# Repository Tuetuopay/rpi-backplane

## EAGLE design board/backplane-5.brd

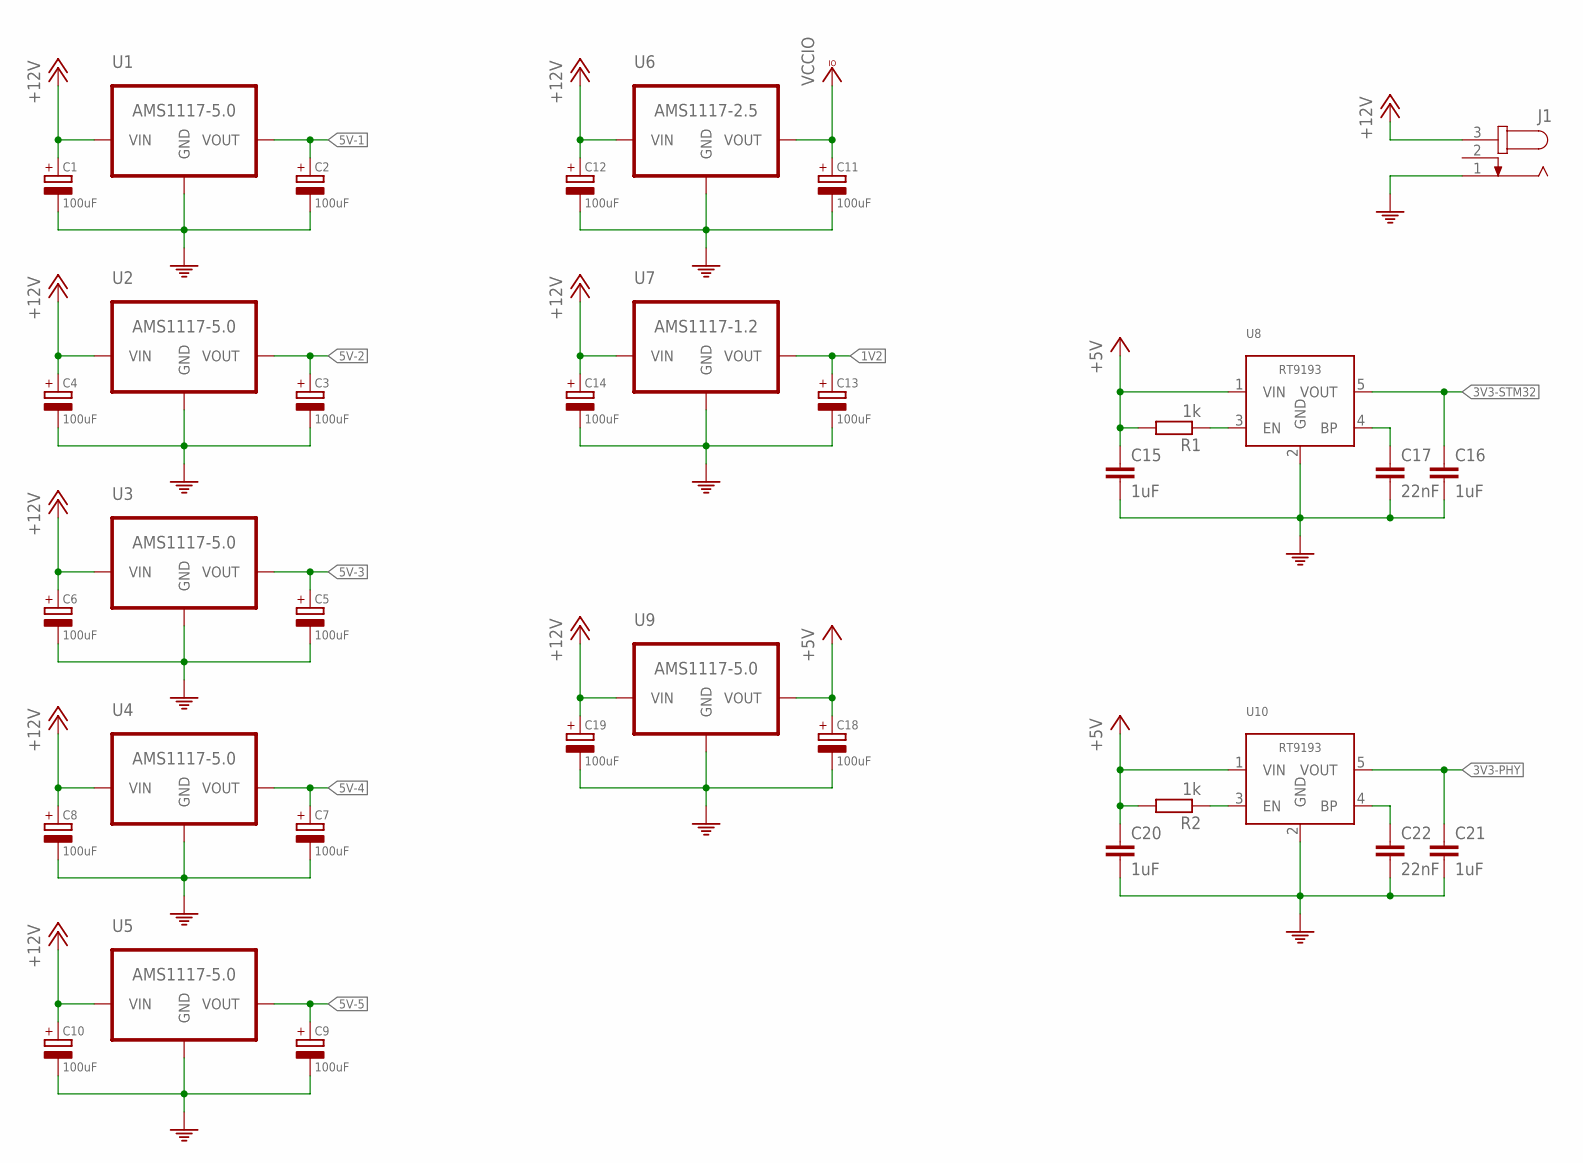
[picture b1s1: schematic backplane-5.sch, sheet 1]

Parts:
C1, C2, C3, C4, C5, C6, C7, C8, C9, C10, C11, C12, C13, C14, C18, C19: 100uF; CAP-D6.3
C15, C16, C20, C21: 1uF; C0603
C17, C22: 22nF; C0603
J1: JACK-PLUG0; SPC4077
R1, R2: 1k; R0603
U1, U2, U3, U4, U5, U9: AMS1117-5.0; SOT223
U6: AMS1117-2.5; SOT223
U7: AMS1117-1.2; SOT223
U8, U10: RT9193; SOT23-5

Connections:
1V2: C13.P (POS), U7.2 (VOUT); also elsewhere on the board
3V3-PHY: C21.1, U10.5 (VOUT); also elsewhere on the board
3V3-STM32: C16.1, U8.5 (VOUT)
5V-1: C2.P (POS), U1.2 (VOUT); also elsewhere on the board
5V-2: C3.P (POS), U2.2 (VOUT); also elsewhere on the board
5V-3: C5.P (POS), U3.2 (VOUT); also elsewhere on the board
5V-4: C7.P (POS), U4.2 (VOUT); also elsewhere on the board
5V-5: C9.P (POS), U5.2 (VOUT); also elsewhere on the board
+5V: C15.1, C18.P (POS), C20.1, R1.2, R2.2, U8.1 (VIN), U9.2 (VOUT), U10.1 (VIN)
+12V: C1.P (POS), C4.P (POS), C6.P (POS), C8.P (POS), C10.P (POS), C12.P (POS), C14.P (POS), C19.P (POS), J1.3, U1.3 (VIN), U2.3 (VIN), U3.3 (VIN), U4.3 (VIN), U5.3 (VIN), U6.3 (VIN), U7.3 (VIN), U9.3 (VIN)
GND: C1.N (NEG), C2.N (NEG), C3.N (NEG), C4.N (NEG), C5.N (NEG), C6.N (NEG), C7.N (NEG), C8.N (NEG), C9.N (NEG), C10.N (NEG), C11.N (NEG), C12.N (NEG), C13.N (NEG), C14.N (NEG), C15.2, C16.2, C17.2, C18.N (NEG), C19.N (NEG), C20.2, C21.2, C22.2, J1.1, U1.1 (GND), U2.1 (GND), U3.1 (GND), U4.1 (GND), U5.1 (GND), U6.1 (GND), U7.1 (GND), U8.2 (GND), U9.1 (GND), U10.2 (GND); also elsewhere on the board
unnamed: C17.1, U8.4 (BP)
unnamed: R1.1, U8.3 (EN)
unnamed: C22.1, U10.4 (BP)
unnamed: R2.1, U10.3 (EN)
VCCIO: C11.P (POS), U6.2 (VOUT); also elsewhere on the board

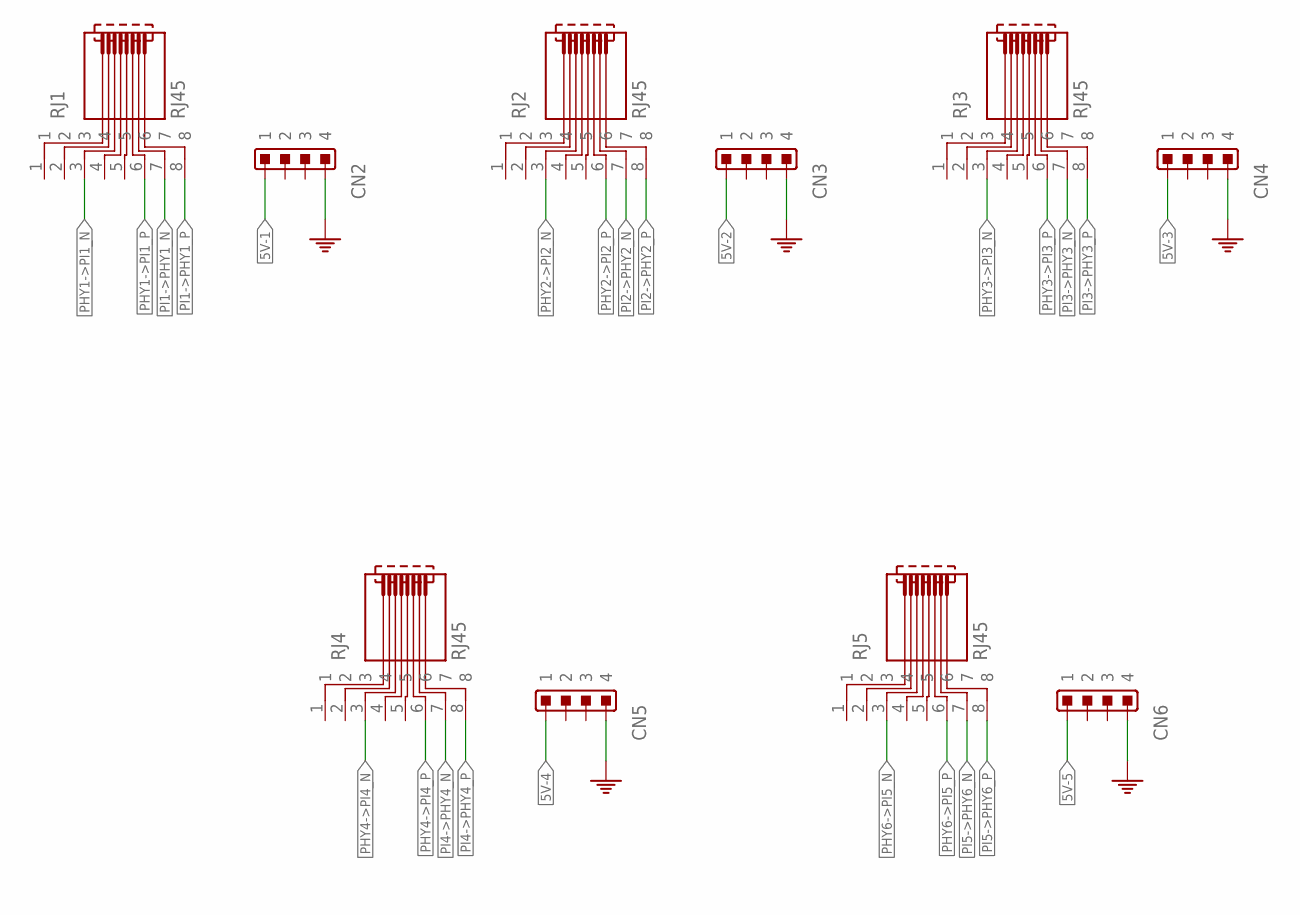
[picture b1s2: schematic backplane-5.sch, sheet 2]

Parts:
CN2, CN3, CN4, CN5, CN6: 4PINCONNFEMALE-1.6; 4PINCONN-FEMALE-1.6
RJ1, RJ2, RJ3, RJ4, RJ5: RJ45PLUG; RJ45MALE

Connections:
5V-1: CN2.1@1 (1), CN2.1@2 (1); also elsewhere on the board
5V-2: CN3.1@1 (1), CN3.1@2 (1); also elsewhere on the board
5V-3: CN4.1@1 (1), CN4.1@2 (1); also elsewhere on the board
5V-4: CN5.1@1 (1), CN5.1@2 (1); also elsewhere on the board
5V-5: CN6.1@1 (1), CN6.1@2 (1); also elsewhere on the board
GND: CN2.4@1 (4), CN2.4@2 (4), CN3.4@1 (4), CN3.4@2 (4), CN4.4@1 (4), CN4.4@2 (4), CN5.4@1 (4), CN5.4@2 (4), CN6.4@1 (4), CN6.4@2 (4); also elsewhere on the board
PHY1->PI1_N: RJ1.3; also elsewhere on the board
PHY1->PI1_P: RJ1.6; also elsewhere on the board
PHY2->PI2_N: RJ2.3; also elsewhere on the board
PHY2->PI2_P: RJ2.6; also elsewhere on the board
PHY3->PI3_N: RJ3.3; also elsewhere on the board
PHY3->PI3_P: RJ3.6; also elsewhere on the board
PHY4->PI4_N: RJ4.3; also elsewhere on the board
PHY4->PI4_P: RJ4.6; also elsewhere on the board
PHY6->PI5_N: RJ5.3; also elsewhere on the board
PHY6->PI5_P: RJ5.6; also elsewhere on the board
PI1->PHY1_N: RJ1.7; also elsewhere on the board
PI1->PHY1_P: RJ1.8; also elsewhere on the board
PI2->PHY2_N: RJ2.7; also elsewhere on the board
PI2->PHY2_P: RJ2.8; also elsewhere on the board
PI3->PHY3_N: RJ3.7; also elsewhere on the board
PI3->PHY3_P: RJ3.8; also elsewhere on the board
PI4->PHY4_N: RJ4.7; also elsewhere on the board
PI4->PHY4_P: RJ4.8; also elsewhere on the board
PI5->PHY6_N: RJ5.7; also elsewhere on the board
PI5->PHY6_P: RJ5.8; also elsewhere on the board

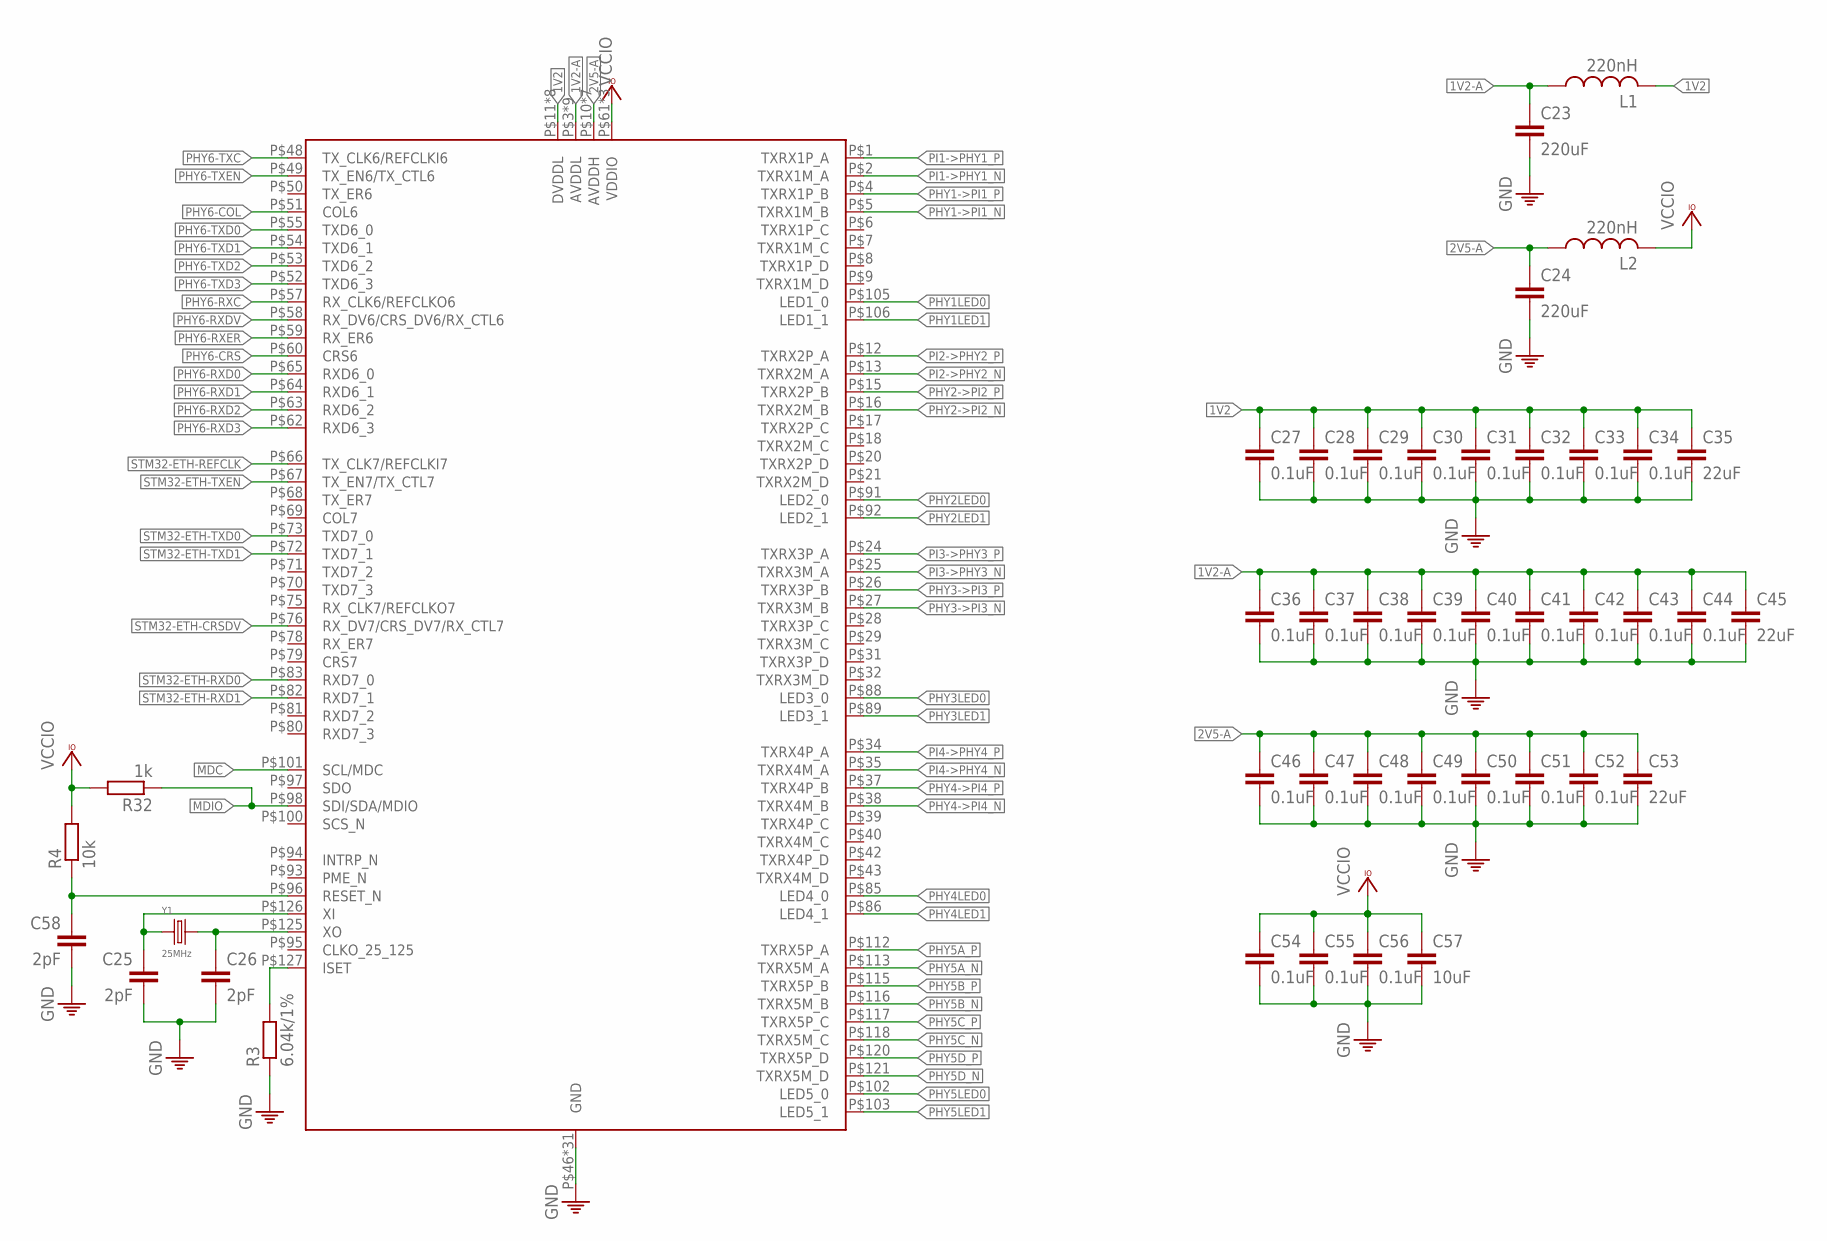
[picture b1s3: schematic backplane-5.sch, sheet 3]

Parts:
C23, C24: 220uF; 0603
C25, C26, C58: 2pF; 0603
C27, C28, C29, C30, C31, C32, C33, C34, C36, C37, C38, C39, C40, C41, C42, C43, C44, C46, C47, C48, C49, C50, C51, C52, C54, C55, C56: 0.1uF; 0603
C35, C45, C53: 22uF; 0603
C57: 10uF; 0603
L1, L2: 220nH; 1210
R3: 6.04k/1%; R0603
R4: 10k; R0603
R32: 1k; R0603
U11: KSZ9897; TQFP-128
Y1: 25MHz; XTAL-2-SMD

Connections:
1V2: C27.1, C28.1, C29.1, C30.1, C31.1, C32.1, C33.1, C34.1, C35.1, L1.2, U11.P$11 (DVDDL), U11.P$23 (DVDDL), U11.P$45 (DVDDL), U11.P$56 (DVDDL), U11.P$74 (DVDDL), U11.P$87 (DVDDL), U11.P$104 (DVDDL), U11.P$110 (DVDDL); also elsewhere on the board
1V2-A: C23.1, C36.1, C37.1, C38.1, C39.1, C40.1, C41.1, C42.1, C43.1, C44.1, C45.1, L1.1, U11.P$3 (AVDDL), U11.P$14 (AVDDL), U11.P$19 (AVDDL), U11.P$30 (AVDDL), U11.P$36 (AVDDL), U11.P$41 (AVDDL), U11.P$114 (AVDDL), U11.P$119 (AVDDL), U11.P$124 (AVDDL)
2V5-A: C24.1, C46.1, C47.1, C48.1, C49.1, C50.1, C51.1, C52.1, C53.1, L2.1, U11.P$10 (AVDDH), U11.P$22 (AVDDH), U11.P$33 (AVDDH), U11.P$44 (AVDDH), U11.P$111 (AVDDH), U11.P$122 (AVDDH), U11.P$128 (AVDDH)
GND: C23.2, C24.2, C25.2, C26.2, C27.2, C28.2, C29.2, C30.2, C31.2, C32.2, C33.2, C34.2, C35.2, C36.2, C37.2, C38.2, C39.2, C40.2, C41.2, C42.2, C43.2, C44.2, C45.2, C46.2, C47.2, C48.2, C49.2, C50.2, C51.2, C52.2, C53.2, C54.2, C55.2, C56.2, C57.2, C58.2, R3.1, U11.P$46 (GND), U11.P$47 (GND), U11.P$84 (GND), U11.P$107 (GND), U11.P$109 (GND), U11.P$123 (GND), U11.P$129 (GND), U11.P$130 (GND), U11.P$131 (GND), U11.P$132 (GND), U11.P$133 (GND), U11.P$134 (GND), U11.P$135 (GND), U11.P$136 (GND), U11.P$137 (GND), U11.P$138 (GND), U11.P$139 (GND), U11.P$140 (GND), U11.P$141 (GND), U11.P$142 (GND), U11.P$143 (GND), U11.P$144 (GND), U11.P$145 (GND), U11.P$146 (GND), U11.P$147 (GND), U11.P$148 (GND), U11.P$149 (GND), U11.P$150 (GND), U11.P$151 (GND), U11.P$152 (GND), U11.P$153 (GND); also elsewhere on the board
MDC: U11.P$101 (SCL/MDC); also elsewhere on the board
MDIO: R32.1, U11.P$98 (SDI/SDA/MDIO); also elsewhere on the board
unnamed: C25.1, U11.P$126 (XI), Y1.P$2
unnamed: C26.1, U11.P$125 (XO), Y1.P$1
unnamed: R3.2, U11.P$127 (ISET)
unnamed: C58.1, R4.1, U11.P$96 (RESET_N)
PHY1->PI1_N: U11.P$5 (TXRX1M_B); also elsewhere on the board
PHY1->PI1_P: U11.P$4 (TXRX1P_B); also elsewhere on the board
PHY1LED0: U11.P$105 (LED1_0); also elsewhere on the board
PHY1LED1: U11.P$106 (LED1_1); also elsewhere on the board
PHY2->PI2_N: U11.P$16 (TXRX2M_B); also elsewhere on the board
PHY2->PI2_P: U11.P$15 (TXRX2P_B); also elsewhere on the board
PHY2LED0: U11.P$91 (LED2_0); also elsewhere on the board
PHY2LED1: U11.P$92 (LED2_1); also elsewhere on the board
PHY3->PI3_N: U11.P$27 (TXRX3M_B); also elsewhere on the board
PHY3->PI3_P: U11.P$26 (TXRX3P_B); also elsewhere on the board
PHY3LED0: U11.P$88 (LED3_0); also elsewhere on the board
PHY3LED1: U11.P$89 (LED3_1); also elsewhere on the board
PHY4->PI4_N: U11.P$38 (TXRX4M_B); also elsewhere on the board
PHY4->PI4_P: U11.P$37 (TXRX4P_B); also elsewhere on the board
PHY4LED0: U11.P$85 (LED4_0); also elsewhere on the board
PHY4LED1: U11.P$86 (LED4_1); also elsewhere on the board
PHY5A_N: U11.P$113 (TXRX5M_A); also elsewhere on the board
PHY5A_P: U11.P$112 (TXRX5P_A); also elsewhere on the board
PHY5B_N: U11.P$116 (TXRX5M_B); also elsewhere on the board
PHY5B_P: U11.P$115 (TXRX5P_B); also elsewhere on the board
PHY5C_N: U11.P$118 (TXRX5M_C); also elsewhere on the board
PHY5C_P: U11.P$117 (TXRX5P_C); also elsewhere on the board
PHY5D_N: U11.P$121 (TXRX5M_D); also elsewhere on the board
PHY5D_P: U11.P$120 (TXRX5P_D); also elsewhere on the board
PHY5LED0: U11.P$102 (LED5_0); also elsewhere on the board
PHY5LED1: U11.P$103 (LED5_1); also elsewhere on the board
PHY6-COL: U11.P$51 (COL6); also elsewhere on the board
PHY6-CRS: U11.P$60 (CRS6); also elsewhere on the board
PHY6-RXC: U11.P$57 (RX_CLK6/REFCLKO6); also elsewhere on the board
PHY6-RXD0: U11.P$65 (RXD6_0); also elsewhere on the board
PHY6-RXD1: U11.P$64 (RXD6_1); also elsewhere on the board
PHY6-RXD2: U11.P$63 (RXD6_2); also elsewhere on the board
PHY6-RXD3: U11.P$62 (RXD6_3); also elsewhere on the board
PHY6-RXDV: U11.P$58 (RX_DV6/CRS_DV6/RX_CTL6); also elsewhere on the board
PHY6-RXER: U11.P$59 (RX_ER6); also elsewhere on the board
PHY6-TXC: U11.P$48 (TX_CLK6/REFCLKI6); also elsewhere on the board
PHY6-TXD0: U11.P$55 (TXD6_0); also elsewhere on the board
PHY6-TXD1: U11.P$54 (TXD6_1); also elsewhere on the board
PHY6-TXD2: U11.P$53 (TXD6_2); also elsewhere on the board
PHY6-TXD3: U11.P$52 (TXD6_3); also elsewhere on the board
PHY6-TXEN: U11.P$49 (TX_EN6/TX_CTL6); also elsewhere on the board
PI1->PHY1_N: U11.P$2 (TXRX1M_A); also elsewhere on the board
PI1->PHY1_P: U11.P$1 (TXRX1P_A); also elsewhere on the board
PI2->PHY2_N: U11.P$13 (TXRX2M_A); also elsewhere on the board
PI2->PHY2_P: U11.P$12 (TXRX2P_A); also elsewhere on the board
PI3->PHY3_N: U11.P$25 (TXRX3M_A); also elsewhere on the board
PI3->PHY3_P: U11.P$24 (TXRX3P_A); also elsewhere on the board
PI4->PHY4_N: U11.P$35 (TXRX4M_A); also elsewhere on the board
PI4->PHY4_P: U11.P$34 (TXRX4P_A); also elsewhere on the board
STM32-ETH-CRSDV: U11.P$76 (RX_DV7/CRS_DV7/RX_CTL7); also elsewhere on the board
STM32-ETH-REFCLK: U11.P$66 (TX_CLK7/REFCLKI7); also elsewhere on the board
STM32-ETH-RXD0: U11.P$83 (RXD7_0); also elsewhere on the board
STM32-ETH-RXD1: U11.P$82 (RXD7_1); also elsewhere on the board
STM32-ETH-TXD0: U11.P$73 (TXD7_0); also elsewhere on the board
STM32-ETH-TXD1: U11.P$72 (TXD7_1); also elsewhere on the board
STM32-ETH-TXEN: U11.P$67 (TX_EN7/TX_CTL7); also elsewhere on the board
VCCIO: C54.1, C55.1, C56.1, C57.1, L2.2, R4.2, R32.2, U11.P$61 (VDDIO), U11.P$77 (VDDIO), U11.P$99 (VDDIO); also elsewhere on the board

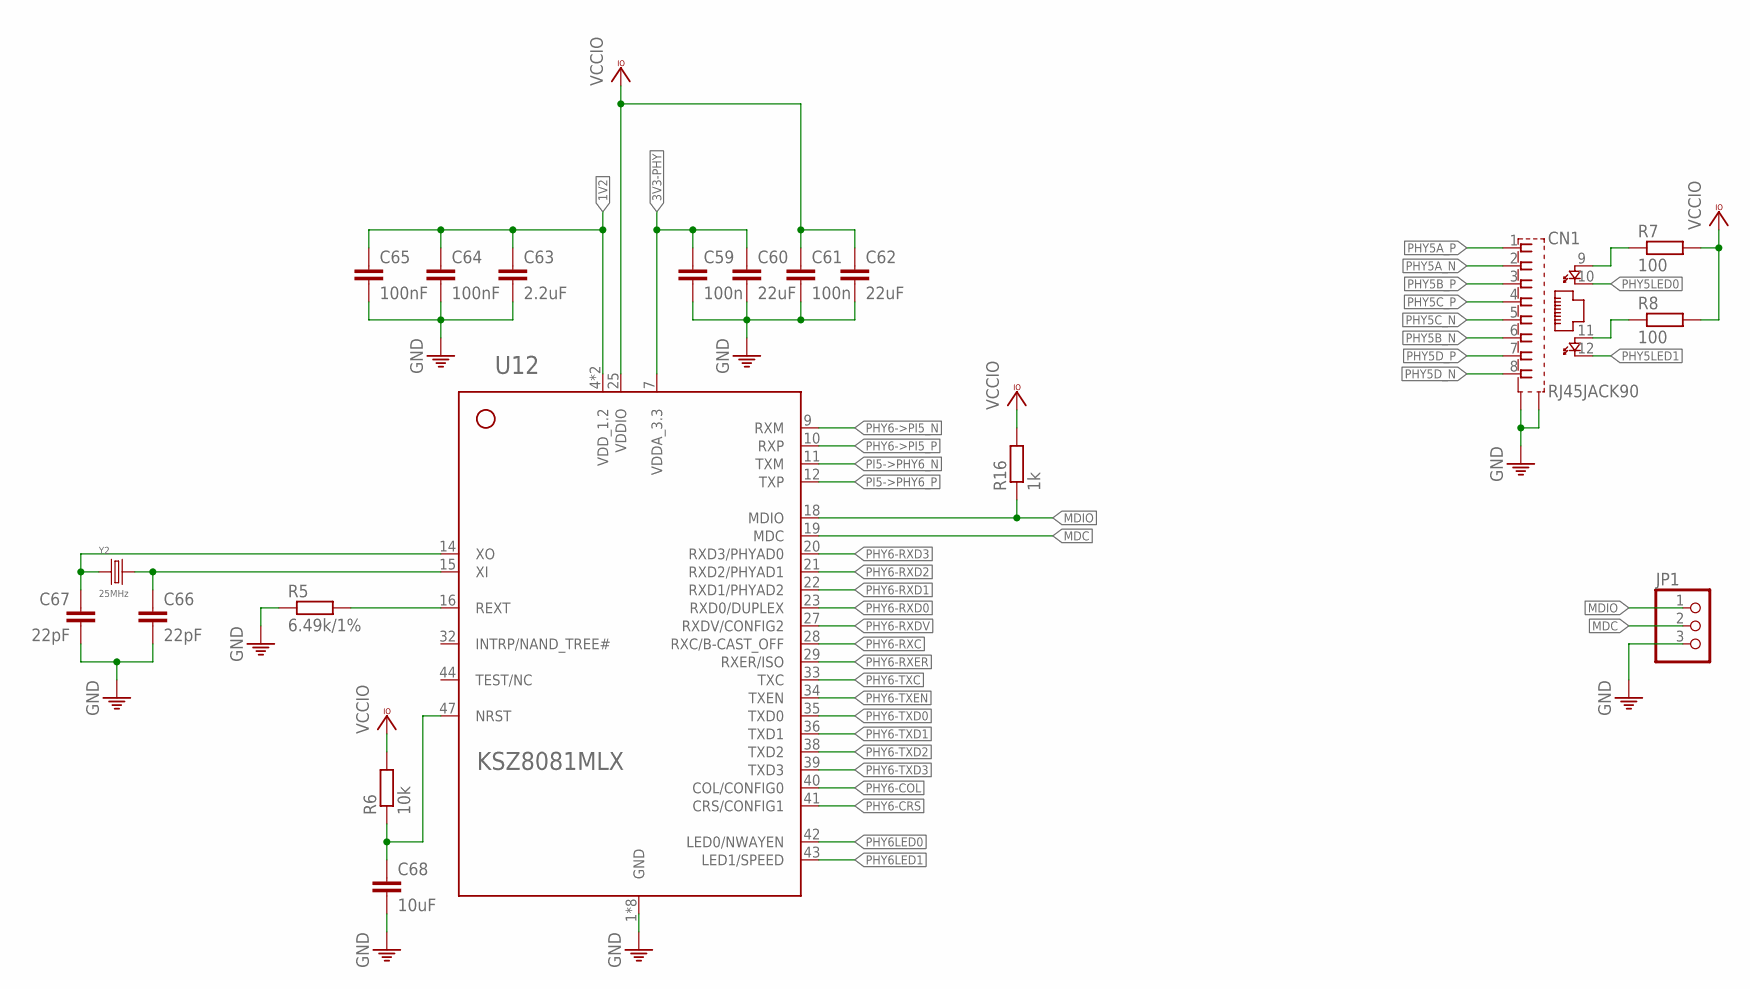
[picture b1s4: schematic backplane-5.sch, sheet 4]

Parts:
C59, C61: 100n; 0603
C60, C62: 22uF; 0603
C63: 2.2uF; 0603
C64, C65: 100nF; 0603
C66, C67: 22pF; 0603
C68: 10uF; 0603
CN1: RJ45JACK90
JP1: PINHD-1X3; 1X03
R5: 6.49k/1%; R0603
R6: 10k; R0603
R7, R8: 100; R0603
R16: 1k; R0603
U12: KSZ8081MLX; LQFP-48
Y2: 25MHz; XTAL-2-SMD

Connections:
1V2: C63.1, C64.1, C65.1, U12.4 (VDD_1.2), U12.31 (VDD_1.2); also elsewhere on the board
3V3-PHY: C59.1, C60.1, U12.7 (VDDA_3.3); also elsewhere on the board
GND: C59.2, C60.2, C61.2, C62.2, C63.2, C64.2, C65.2, C66.2, C67.2, C68.2, CN1.S@1 (S1), CN1.S@2 (S2), JP1.3, R5.1, U12.1 (GND), U12.2 (GND), U12.3 (GND), U12.13 (GND), U12.17 (GND), U12.24 (GND), U12.30 (GND), U12.37 (GND); also elsewhere on the board
MDC: JP1.2, U12.19 (MDC); also elsewhere on the board
MDIO: JP1.1, R16.1, U12.18 (MDIO); also elsewhere on the board
unnamed: C66.1, U12.15 (XI), Y2.P$1
unnamed: C67.1, U12.14 (XO), Y2.P$2
unnamed: R5.2, U12.16 (REXT)
unnamed: C68.1, R6.1, U12.47 (NRST)
unnamed: CN1.9 (YELLOW_A), R7.1
unnamed: CN1.11 (GREEN_A), R8.1
PHY5A_N: CN1.2; also elsewhere on the board
PHY5A_P: CN1.1; also elsewhere on the board
PHY5B_N: CN1.6; also elsewhere on the board
PHY5B_P: CN1.3; also elsewhere on the board
PHY5C_N: CN1.5; also elsewhere on the board
PHY5C_P: CN1.4; also elsewhere on the board
PHY5D_N: CN1.8; also elsewhere on the board
PHY5D_P: CN1.7; also elsewhere on the board
PHY5LED0: CN1.10 (YELLOW_C); also elsewhere on the board
PHY5LED1: CN1.12 (GREEN_C); also elsewhere on the board
PHY6->PI5_N: U12.9 (RXM); also elsewhere on the board
PHY6->PI5_P: U12.10 (RXP); also elsewhere on the board
PHY6-COL: U12.40 (COL/CONFIG0); also elsewhere on the board
PHY6-CRS: U12.41 (CRS/CONFIG1); also elsewhere on the board
PHY6-RXC: U12.28 (RXC/B-CAST_OFF); also elsewhere on the board
PHY6-RXD0: U12.23 (RXD0/DUPLEX); also elsewhere on the board
PHY6-RXD1: U12.22 (RXD1/PHYAD2); also elsewhere on the board
PHY6-RXD2: U12.21 (RXD2/PHYAD1); also elsewhere on the board
PHY6-RXD3: U12.20 (RXD3/PHYAD0); also elsewhere on the board
PHY6-RXDV: U12.27 (RXDV/CONFIG2); also elsewhere on the board
PHY6-RXER: U12.29 (RXER/ISO); also elsewhere on the board
PHY6-TXC: U12.33 (TXC); also elsewhere on the board
PHY6-TXD0: U12.35 (TXD0); also elsewhere on the board
PHY6-TXD1: U12.36 (TXD1); also elsewhere on the board
PHY6-TXD2: U12.38 (TXD2); also elsewhere on the board
PHY6-TXD3: U12.39 (TXD3); also elsewhere on the board
PHY6-TXEN: U12.34 (TXEN); also elsewhere on the board
PHY6LED0: U12.42 (LED0/NWAYEN); also elsewhere on the board
PHY6LED1: U12.43 (LED1/SPEED); also elsewhere on the board
PI5->PHY6_N: U12.11 (TXM); also elsewhere on the board
PI5->PHY6_P: U12.12 (TXP); also elsewhere on the board
VCCIO: C61.1, C62.1, R6.2, R7.2, R8.2, R16.2, U12.25 (VDDIO); also elsewhere on the board

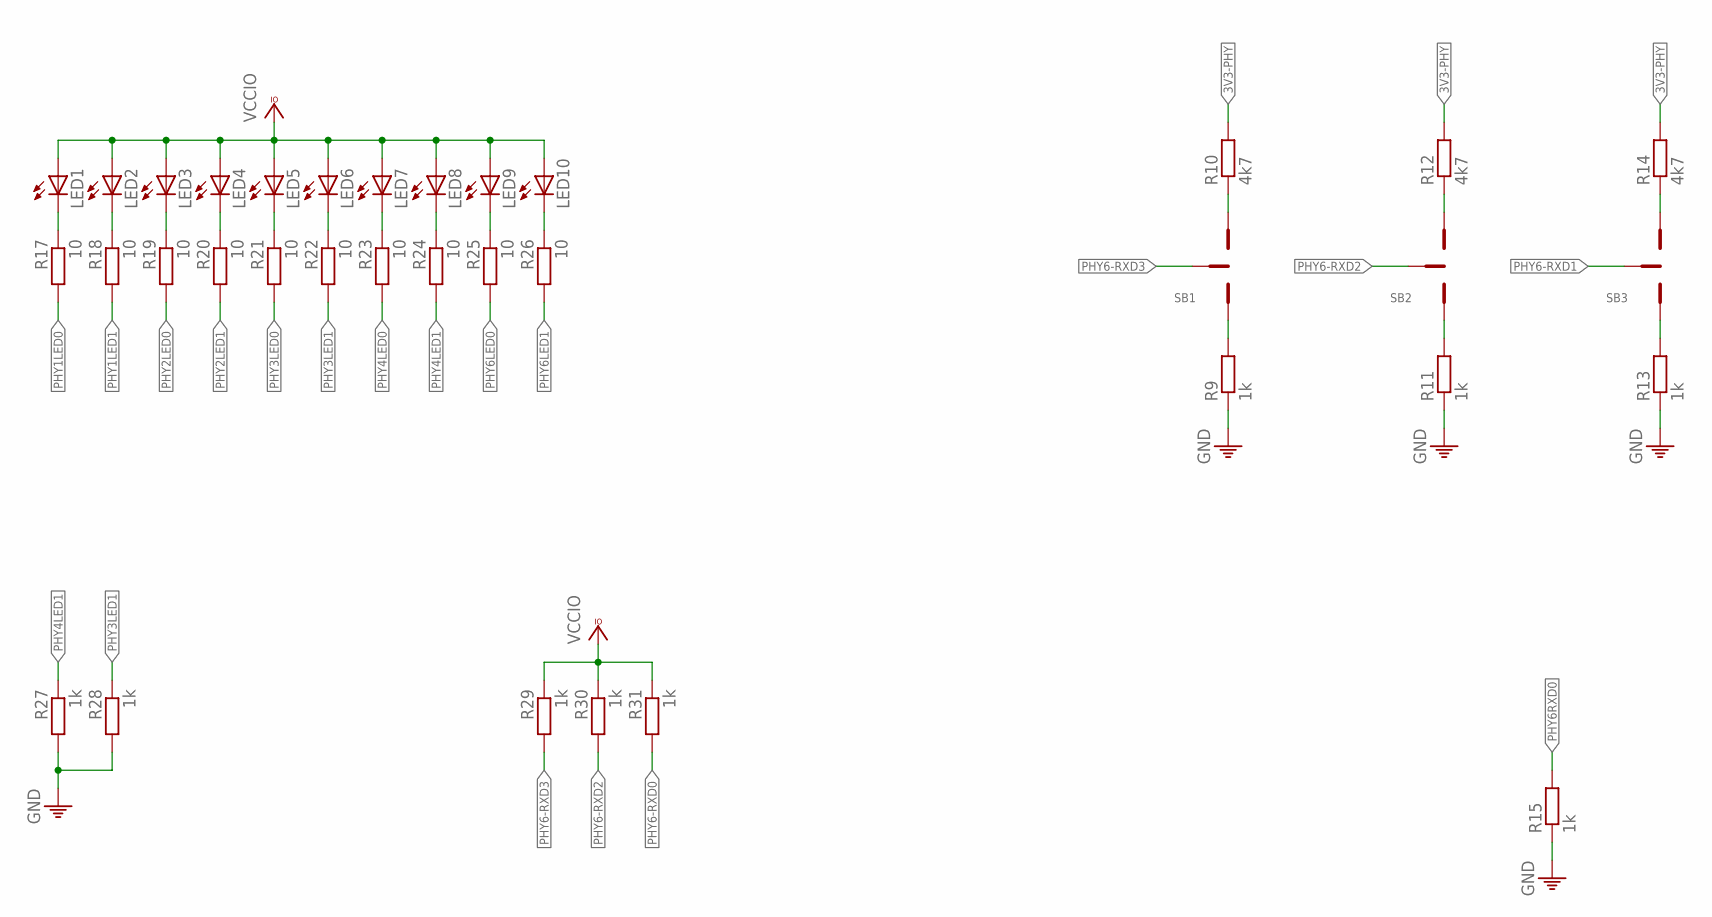
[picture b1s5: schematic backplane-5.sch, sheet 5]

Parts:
LED1, LED2, LED3, LED4, LED5, LED6, LED7, LED8, LED9, LED10: LEDCHIPLED_0603; CHIPLED_0603
R9, R11, R13, R15, R27, R28, R29, R30, R31: 1k; R0603
R10, R12, R14: 4k7; R0603
R17, R18, R19, R20, R21, R22, R23, R24, R25, R26: 10; R0603
SB1, SB2, SB3: SB

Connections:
3V3-PHY: R10.2, R12.2, R14.2; also elsewhere on the board
GND: R9.1, R11.1, R13.1, R15.1, R27.2, R28.2; also elsewhere on the board
unnamed: R11.2, SB2.1
unnamed: R9.2, SB1.1
unnamed: R10.1, SB1.3
unnamed: R12.1, SB2.3
unnamed: R13.2, SB3.1
unnamed: R14.1, SB3.3
unnamed: LED1.C, R17.1
unnamed: LED2.C, R18.1
unnamed: LED3.C, R19.1
unnamed: LED4.C, R20.1
unnamed: LED5.C, R21.1
unnamed: LED6.C, R22.1
unnamed: LED7.C, R23.1
unnamed: LED8.C, R24.1
unnamed: LED9.C, R25.1
unnamed: LED10.C, R26.1
PHY1LED0: R17.2; also elsewhere on the board
PHY1LED1: R18.2; also elsewhere on the board
PHY2LED0: R19.2; also elsewhere on the board
PHY2LED1: R20.2; also elsewhere on the board
PHY3LED0: R21.2; also elsewhere on the board
PHY3LED1: R22.2, R28.1; also elsewhere on the board
PHY4LED0: R23.2; also elsewhere on the board
PHY4LED1: R24.2, R27.1; also elsewhere on the board
PHY6-RXD0: R31.2; also elsewhere on the board
PHY6-RXD1: SB3.2; also elsewhere on the board
PHY6-RXD2: R30.2, SB2.2; also elsewhere on the board
PHY6-RXD3: R29.2, SB1.2; also elsewhere on the board
PHY6LED0: R25.2; also elsewhere on the board
PHY6LED1: R26.2; also elsewhere on the board
PHY6RXD0: R15.2
VCCIO: LED1.A, LED2.A, LED3.A, LED4.A, LED5.A, LED6.A, LED7.A, LED8.A, LED9.A, LED10.A, R29.1, R30.1, R31.1; also elsewhere on the board

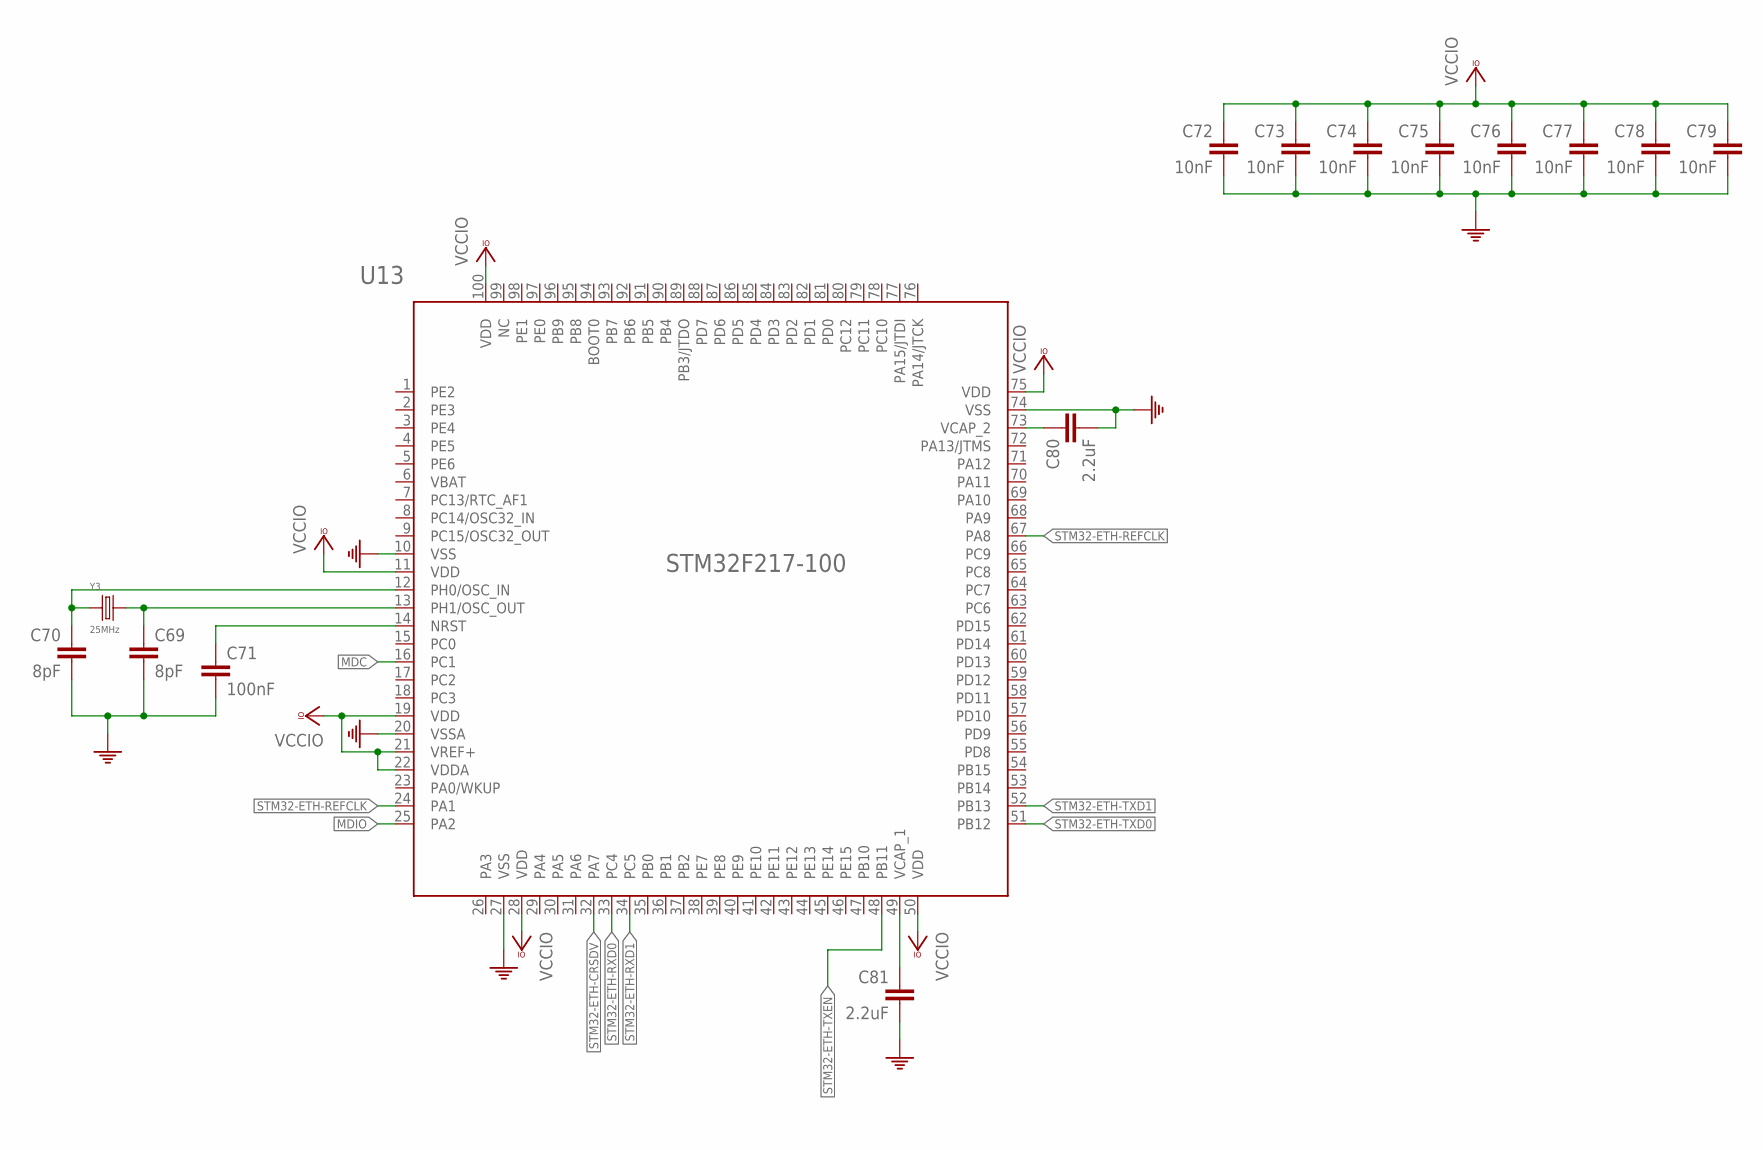
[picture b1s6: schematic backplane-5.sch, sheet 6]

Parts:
C69, C70: 8pF; 0603
C71: 100nF; 0603
C72, C73, C74, C75, C76, C77, C78, C79: 10nF; 0603
C80, C81: 2.2uF; 0805
U13: STM32F217-100; LQFP-100
Y3: 25MHz; XTAL-2-SMD

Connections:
GND: C69.2, C70.2, C71.2, C72.2, C73.2, C74.2, C75.2, C76.2, C77.2, C78.2, C79.2, C80.2, C81.2, U13.10 (VSS), U13.20 (VSSA), U13.27 (VSS), U13.74 (VSS); also elsewhere on the board
MDC: U13.16 (PC1); also elsewhere on the board
MDIO: U13.25 (PA2); also elsewhere on the board
unnamed: C69.1, U13.13 (PH1/OSC_OUT), Y3.P$1
unnamed: C70.1, U13.12 (PH0/OSC_IN), Y3.P$2
unnamed: C71.1, U13.14 (NRST)
unnamed: C80.1, U13.73 (VCAP_2)
unnamed: C81.1, U13.49 (VCAP_1)
STM32-ETH-CRSDV: U13.32 (PA7); also elsewhere on the board
STM32-ETH-REFCLK: U13.24 (PA1), U13.67 (PA8); also elsewhere on the board
STM32-ETH-RXD0: U13.33 (PC4); also elsewhere on the board
STM32-ETH-RXD1: U13.34 (PC5); also elsewhere on the board
STM32-ETH-TXD0: U13.51 (PB12); also elsewhere on the board
STM32-ETH-TXD1: U13.52 (PB13); also elsewhere on the board
STM32-ETH-TXEN: U13.48 (PB11); also elsewhere on the board
VCCIO: C72.1, C73.1, C74.1, C75.1, C76.1, C77.1, C78.1, C79.1, U13.11 (VDD), U13.19 (VDD), U13.21 (VREF+), U13.22 (VDDA), U13.28 (VDD), U13.50 (VDD), U13.75 (VDD), U13.100 (VDD); also elsewhere on the board

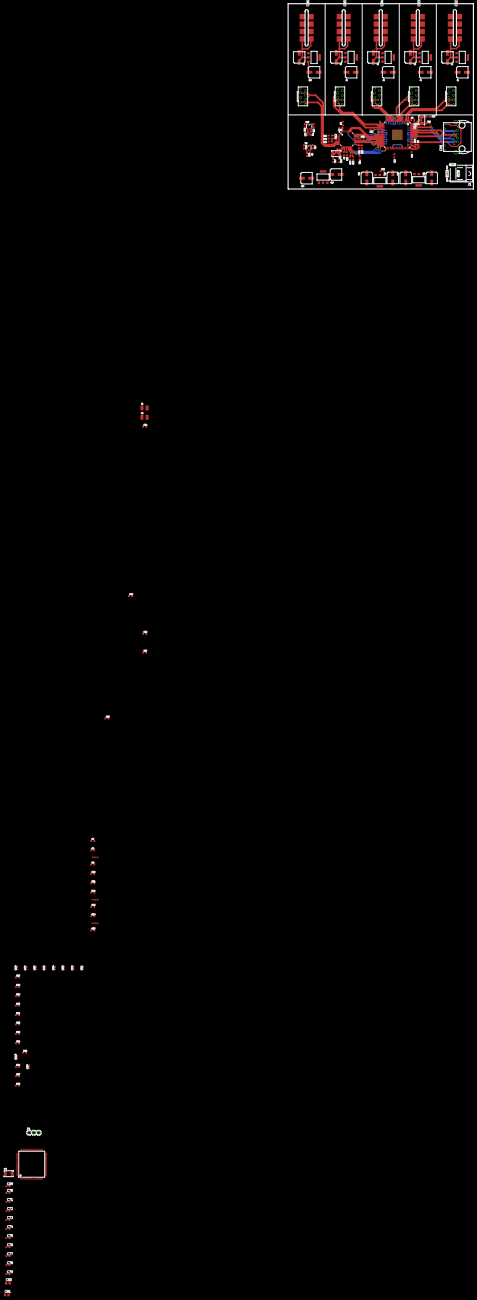
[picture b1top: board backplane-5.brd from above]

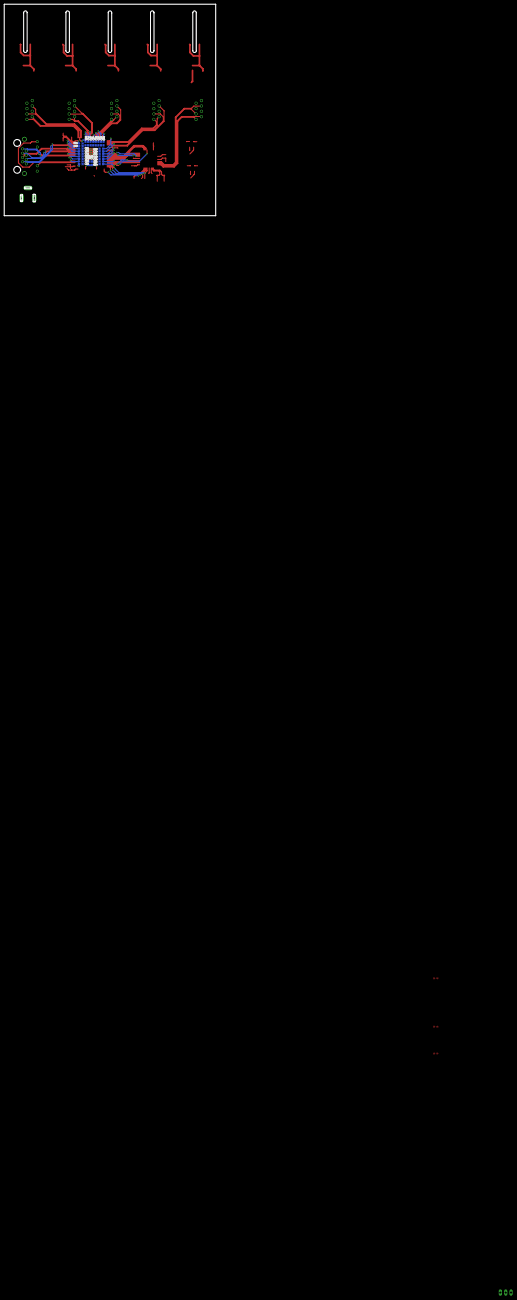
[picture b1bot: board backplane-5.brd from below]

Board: 2 copper layers, 100.0 x 100.0 mm, 157 parts (26 on the bottom side), 113 nets.

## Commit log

2017-09-26 Tweaked some packages and placed RPi conn
2017-09-26 Fixed led connection
2017-09-26 Laid out some psus
2017-09-27 Fixed some errors due to ground on the schematic
2017-09-27 Placed some decoupling caps on the board
2017-09-27 Tweaked a bit the caps
2017-09-27 Fix decoupling for the PHY
2017-09-27 Routed switch resistors
2017-09-27 Connected decoupling caps on the switch
2017-09-27 Routed most ethernet jacks
2017-09-27 Routed the MII interface
    Holy shit.
2017-09-27 Tweaked some decoupling caps
2017-09-28 Routed some config resistors
2017-10-03 Tweaked some traces and updated the library
2017-10-03 Added STM32F217
2017-10-03 Added STM Crystal and fixed some devices
2017-10-03 Fixed the naming of some components (incl. library)
2017-10-03 Added power to the STM32 and its decoupling caps
2017-10-03 Added VCAP capacitors
2017-10-10 Added switch <-> stm32 rmii in schematic
2017-10-14 Added the REFCLK source for switch <-> stm
2017-10-14 Proper supply symbols for some supply rails
2017-10-14 Wired Pis in Gbps and used PHY for ext jack
